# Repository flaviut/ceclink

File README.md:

# CECLink

The CECLink is a small device that can be used to allow a Linux computer to control a TV using the CEC protocol over HDMI. This is particularly helpful for HTPCs, which often do not have the required hardware to do so built-in.

## Why?

What's unique about this device is that it supports higher HDMI bandwidths. It is designed to work with and tested on a 4k, 10-bit HDR, 60FPS signal. This is done through following best practices for high-speed data lines.

While others devices look like this, and are made on a standard PCB (thanks [karl for the photo](https://karlquinsland.com/pulse-eight-hdmi-cec-injector-teardown/)):

This project's design looks a little different, as it follows best practices in the dark arts of RF design:

To be clear, this is not a secret technique! I would love to see others use this technique, and offer an updated commercial version of this device! All the details on how it works are in this source repo under `pcb/`, and I would be happy to talk about it.

## Making your own

### PCB

The hardware is split across two KiCad projects under [`pcb/`](pcb). You will
need to have *both* these boards produced:

* [`pcb/hdmi-breakout`](pcb/hdmi-breakout) — the HDMI passthrough that breaks
  out the CEC and DDC signals. It is a 4-layer board; order it with the
  **JLC04161H-7628 stackup**. The precise stackup is *crucial* for it to work.
* [`pcb/xiao-rp2350-adaptor`](pcb/xiao-rp2350-adaptor) — a simple breakout for the XIAO RP2350
  that connects to the HDMI breakout. This is an ordinary 2-layer board with
  no controlled-impedance requirement, so any standard stackup is fine.

The [latest release](https://github.com/flaviut/ceclink/releases/latest) has
ready-to-order Gerber and drill archives: `adapter.zip` for the XIAO RP2350 adapter
and `hdmi-breakout.zip` for the HDMI board.

Gerber and drill archives for each board can be generated with
[`jlcpcb_fab.py`](jlcpcb_fab.py).

Additional BOM (parts to source separately on top of the fabricated boards):

| Count | Part |
| ----- | ---- |
| 2 | HDMI Type-A receptacle (Molex 208658-1001, LCSC C138388) |
| 2 | 0603 100kΩ resistor |
| 1 | XIAO RP2350 |
| 2 | 1×9 2.54mm male pin header strip |
| 2 | 1×9 2.54mm female header / socket strip |
| 2 | M3 × 16mm socket head cap screw |
| 2 | M3 nut |

Remember that you can easily cut a longer 2.54mm header to size with some snips.

### Initial flash

Download `firmware.uf2` from the
[latest release](https://github.com/flaviut/ceclink/releases/latest).

Hold the BOOT button while connecting the USB cable. Once powered, you should see a new drive on your computer. Copy-paste the `.uf2` file over, and your device should be flashed.

#### CLI alternative

```sh
picotool load -v -x ceclink.uf2
```

### Operating system integration

This project tries to make use of the operating system drivers for the bulk of the integration, but this is unfortunately not fully sufficient. On Linux, `inputattach` connects the CEC serial interface to the Pulse-Eight kernel driver. A separate helper reads the HDMI physical address from the status interface and applies it to the kernel's CEC device.

#### Generic Linux installation

These instructions use systemd and udev to start the adapter automatically when it is plugged in, including after reboot.

Install the dependencies for your distribution:

| Distribution family | Install command |
| --- | --- |
| Debian / Ubuntu | `sudo apt install curl inputattach python3-serial ddcutil v4l-utils` |
| Fedora | `sudo dnf install curl linuxconsoletools python3-pyserial ddcutil v4l-utils` |
| Arch Linux | `sudo pacman -S curl linuxconsole python-pyserial ddcutil v4l-utils` |

Download the physical-address helper into `/opt/ceclink` and configure the kernel modules to load at boot:

```sh
sudo install -d -m755 /opt/ceclink
sudo curl --fail --location https://raw.githubusercontent.com/flaviut/ceclink/HEAD/nix/physical-address.py -o /opt/ceclink/physical-address.py
sudo curl --fail --location https://raw.githubusercontent.com/flaviut/ceclink/HEAD/linux/ceclink.conf -o /etc/modules-load.d/ceclink.conf
sudo modprobe pulse8-cec
sudo modprobe i2c-dev
```

If `modprobe pulse8-cec` reports that the module is missing, your kernel needs the Pulse-Eight CEC driver (`CONFIG_USB_PULSE8_CEC`). Install your distribution's additional kernel modules package or use a kernel that includes this driver before continuing.

Install the two systemd service templates. The first attaches the CEC control port to the kernel driver; the second keeps the kernel's HDMI physical address synchronized with the adapter:

```sh
sudo curl --fail --location https://raw.githubusercontent.com/flaviut/ceclink/HEAD/linux/pulse8-cec-inputattach@.service -o /etc/systemd/system/pulse8-cec-inputattach@.service

sudo curl --fail --location https://raw.githubusercontent.com/flaviut/ceclink/HEAD/linux/ceclink-physical-address@.service -o /etc/systemd/system/ceclink-physical-address@.service
```

Install the udev rules that start these services for the correct USB interfaces. Interface `00` carries CEC commands; interface `02` carries physical-address status:

```sh
sudo curl --fail --location https://raw.githubusercontent.com/flaviut/ceclink/HEAD/linux/99-ceclink.rules -o /etc/udev/rules.d/99-ceclink.rules
sudo systemctl daemon-reload
sudo udevadm control --reload-rules
```

Connect the adapter in the HDMI path, then unplug and reconnect its USB cable. udev starts both services automatically; no `systemctl enable` is needed. Check that they are running and that the CEC device has a physical address:

```sh
systemctl status 'pulse8-cec-inputattach@*' 'ceclink-physical-address@*'
sudo cec-ctl -d /dev/cec0
```

If you have multiple CEC devices, substitute the adapter's `/dev/cecN` path. To inspect service logs:

```sh
journalctl -b -u 'pulse8-cec-inputattach@*' -u 'ceclink-physical-address@*'
```

#### NixOS integration

Things are much easier on NixOS. Add this repository to your system flake's inputs:

```nix
inputs.ceclink.url = "github:flaviut/ceclink";
```

Include `ceclink` in your flake's `outputs` arguments and add its module to the host's existing `nixosSystem` module list:

```nix
outputs = { nixpkgs, ceclink, ... }: {
  nixosConfigurations.myhost = nixpkgs.lib.nixosSystem {
    modules = [
      ./configuration.nix
      ceclink.nixosModules.default
    ];
  };
};
```

## Development

### Building

```sh
nix develop
cargo build --locked --profile release-with-debug
picotool uf2 convert target/thumbv8m.main-none-eabihf/release-with-debug/ceclink -t elf ceclink.uf2
```

If direnv is enabled in your shell, run `direnv allow` once in this directory to enter the flake dev shell automatically.

For a reproducible production artifact:

```sh
nix build .#firmware
ls result/ceclink.{uf2,elf}
```

Format the Nix and Rust sources with `nix fmt`.

## Connections

| XIAO pin | RP2350 GPIO | Role |
| --- | ---: | --- |
| D9 | GPIO4 | Bidirectional CEC, open drain |
| D4 | GPIO6 | DDC SDA input only |
| D5 | GPIO7 | DDC SCL input only |

D4 and D5 are receive-only GPIO inputs, not I²C master pins. Use a 100kΩ resistor between the HDMI bus and the RP2350.

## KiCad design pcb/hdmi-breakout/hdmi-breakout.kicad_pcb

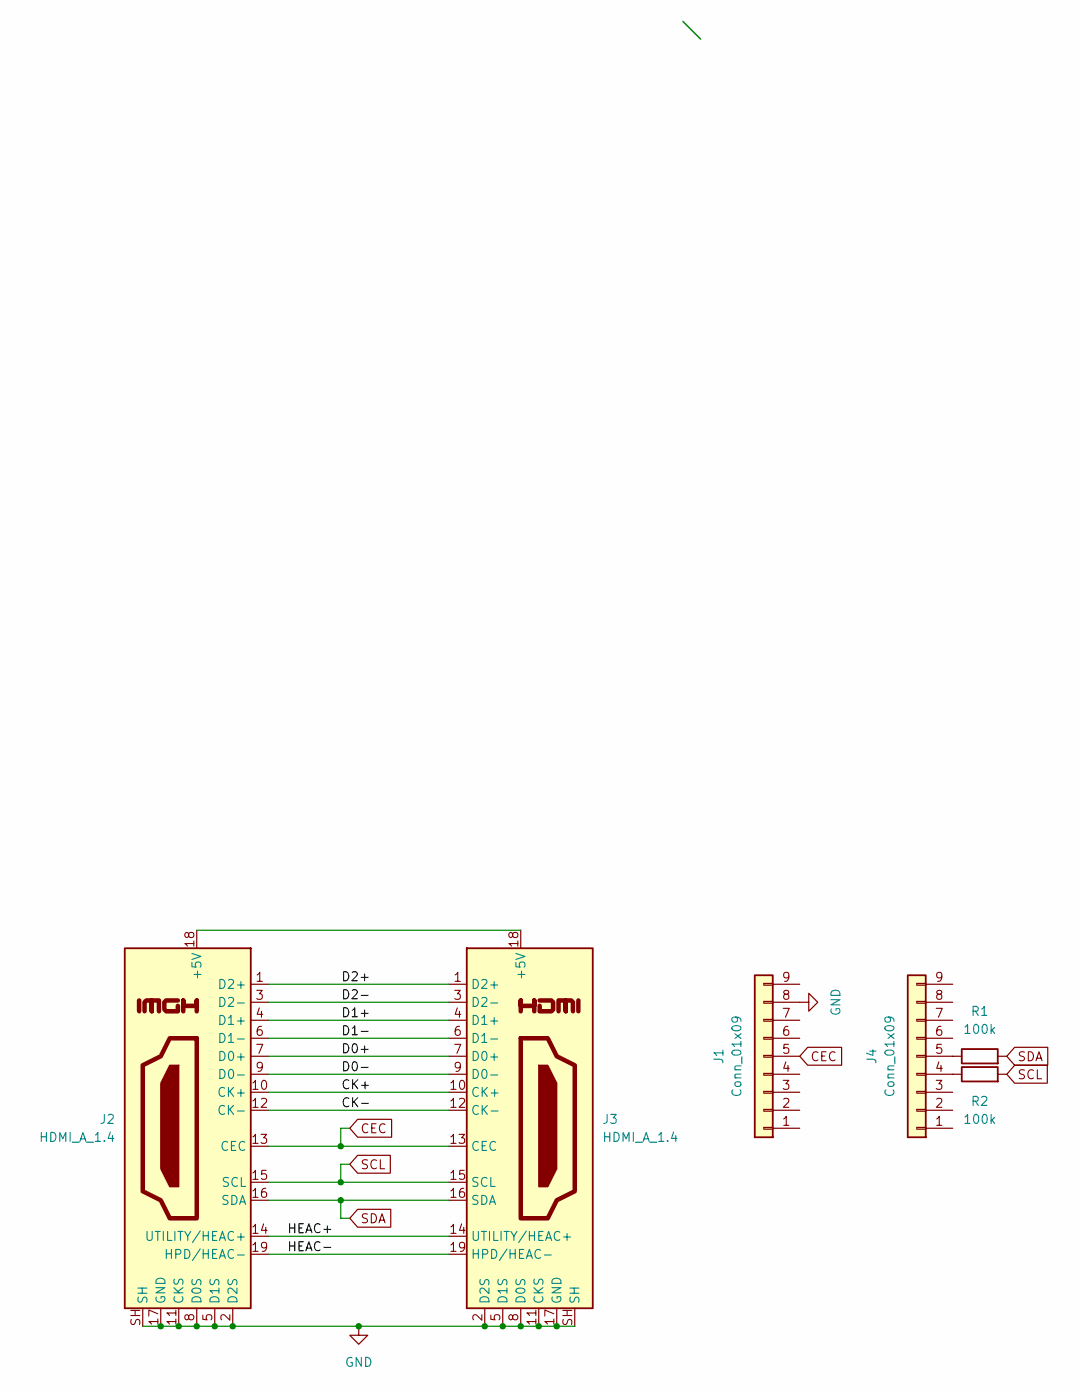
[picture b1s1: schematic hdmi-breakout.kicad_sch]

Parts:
J1, J4: Conn_01x09; PinHeader_1x09_P2.54mm_Vertical; LCSC C2897372
J2, J3: HDMI_A_1.4; HDMI_A_Molex_208658-1001_Horizontal; LCSC C138388
R1, R2: 100k; R_0603_1608Metric_Pad0.98x0.95mm_HandSolder; LCSC C25803

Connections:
/CK+: J2.10 (CK+), J3.10 (CK+)
/CK-: J2.12 (CK-), J3.12 (CK-)
/D0+: J2.7 (D0+), J3.7 (D0+)
/D0-: J2.9 (D0-), J3.9 (D0-)
/D1+: J2.4 (D1+), J3.4 (D1+)
/D1-: J2.6 (D1-), J3.6 (D1-)
/D2+: J2.1 (D2+), J3.1 (D2+)
/D2-: J2.3 (D2-), J3.3 (D2-)
/HEAC+: J2.14 (UTILITY/HEAC+), J3.14 (UTILITY/HEAC+)
/HEAC-: J2.19 (HPD/HEAC-), J3.19 (HPD/HEAC-)
CEC: J1.5, J2.13 (CEC), J3.13 (CEC)
GND: J1.8, J2.2 (D2S), J2.5 (D1S), J2.8 (D0S), J2.11 (CKS), J2.17 (GND), J2.SH, J3.2 (D2S), J3.5 (D1S), J3.8 (D0S), J3.11 (CKS), J3.17 (GND), J3.SH
unnamed: J2.18 (+5V), J3.18 (+5V)
unnamed: J4.4, R2.1
unnamed: J4.5, R1.1
SCL: J2.15 (SCL), J3.15 (SCL), R2.2
SDA: J2.16 (SDA), J3.16 (SDA), R1.2

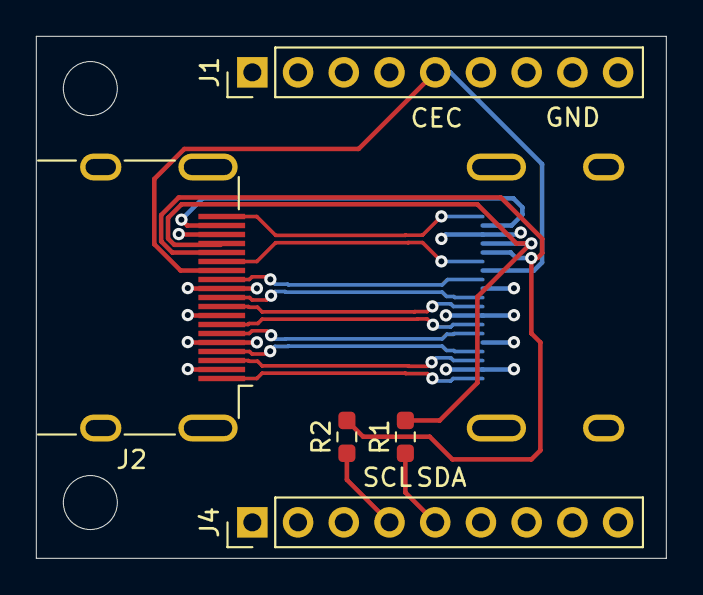
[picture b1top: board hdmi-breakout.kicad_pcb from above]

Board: 4 copper layers, 35.0 x 29.0 mm, 6 parts (1 on the bottom side), 17 nets.

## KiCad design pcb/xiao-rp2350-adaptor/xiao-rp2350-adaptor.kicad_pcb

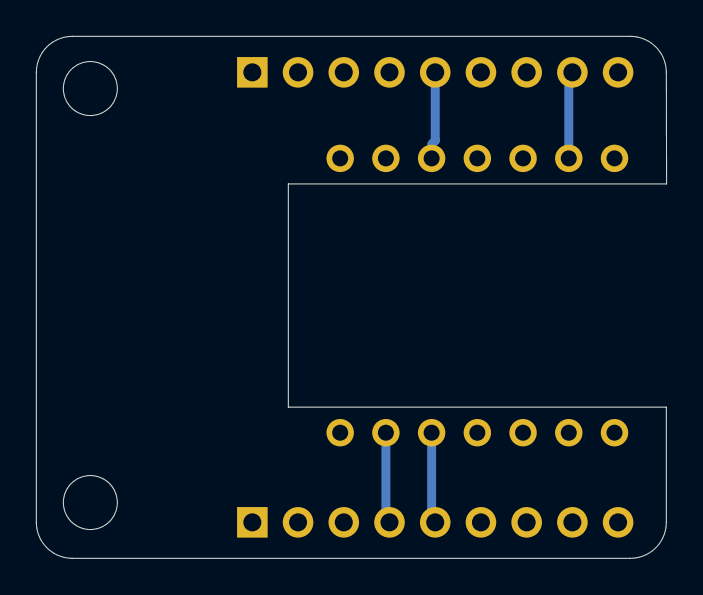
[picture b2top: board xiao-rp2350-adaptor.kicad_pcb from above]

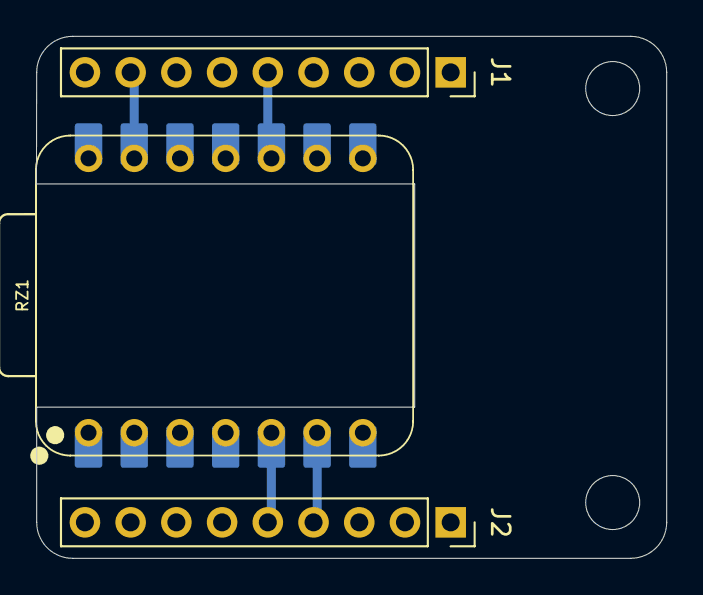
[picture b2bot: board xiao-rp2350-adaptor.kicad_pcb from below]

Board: 2 copper layers, 35.0 x 29.0 mm, 3 parts (3 on the bottom side), 4 nets.

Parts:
J1, J2: Conn_01x09; PinSocket_1x09_P2.54mm_Vertical
RZ1: XIAO-RP2350; XIAO-RP2350-DIP

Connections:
CEC: J1.5, RZ1.10 (GPIO4_D9_SPI0_MISO)
GND: J1.8, RZ1.13 (GND)
SCL: J2.4, RZ1.6 (GPIO7_D5_SCL1)
SDA: J2.5, RZ1.5 (GPIO6_D4_SDA1)
